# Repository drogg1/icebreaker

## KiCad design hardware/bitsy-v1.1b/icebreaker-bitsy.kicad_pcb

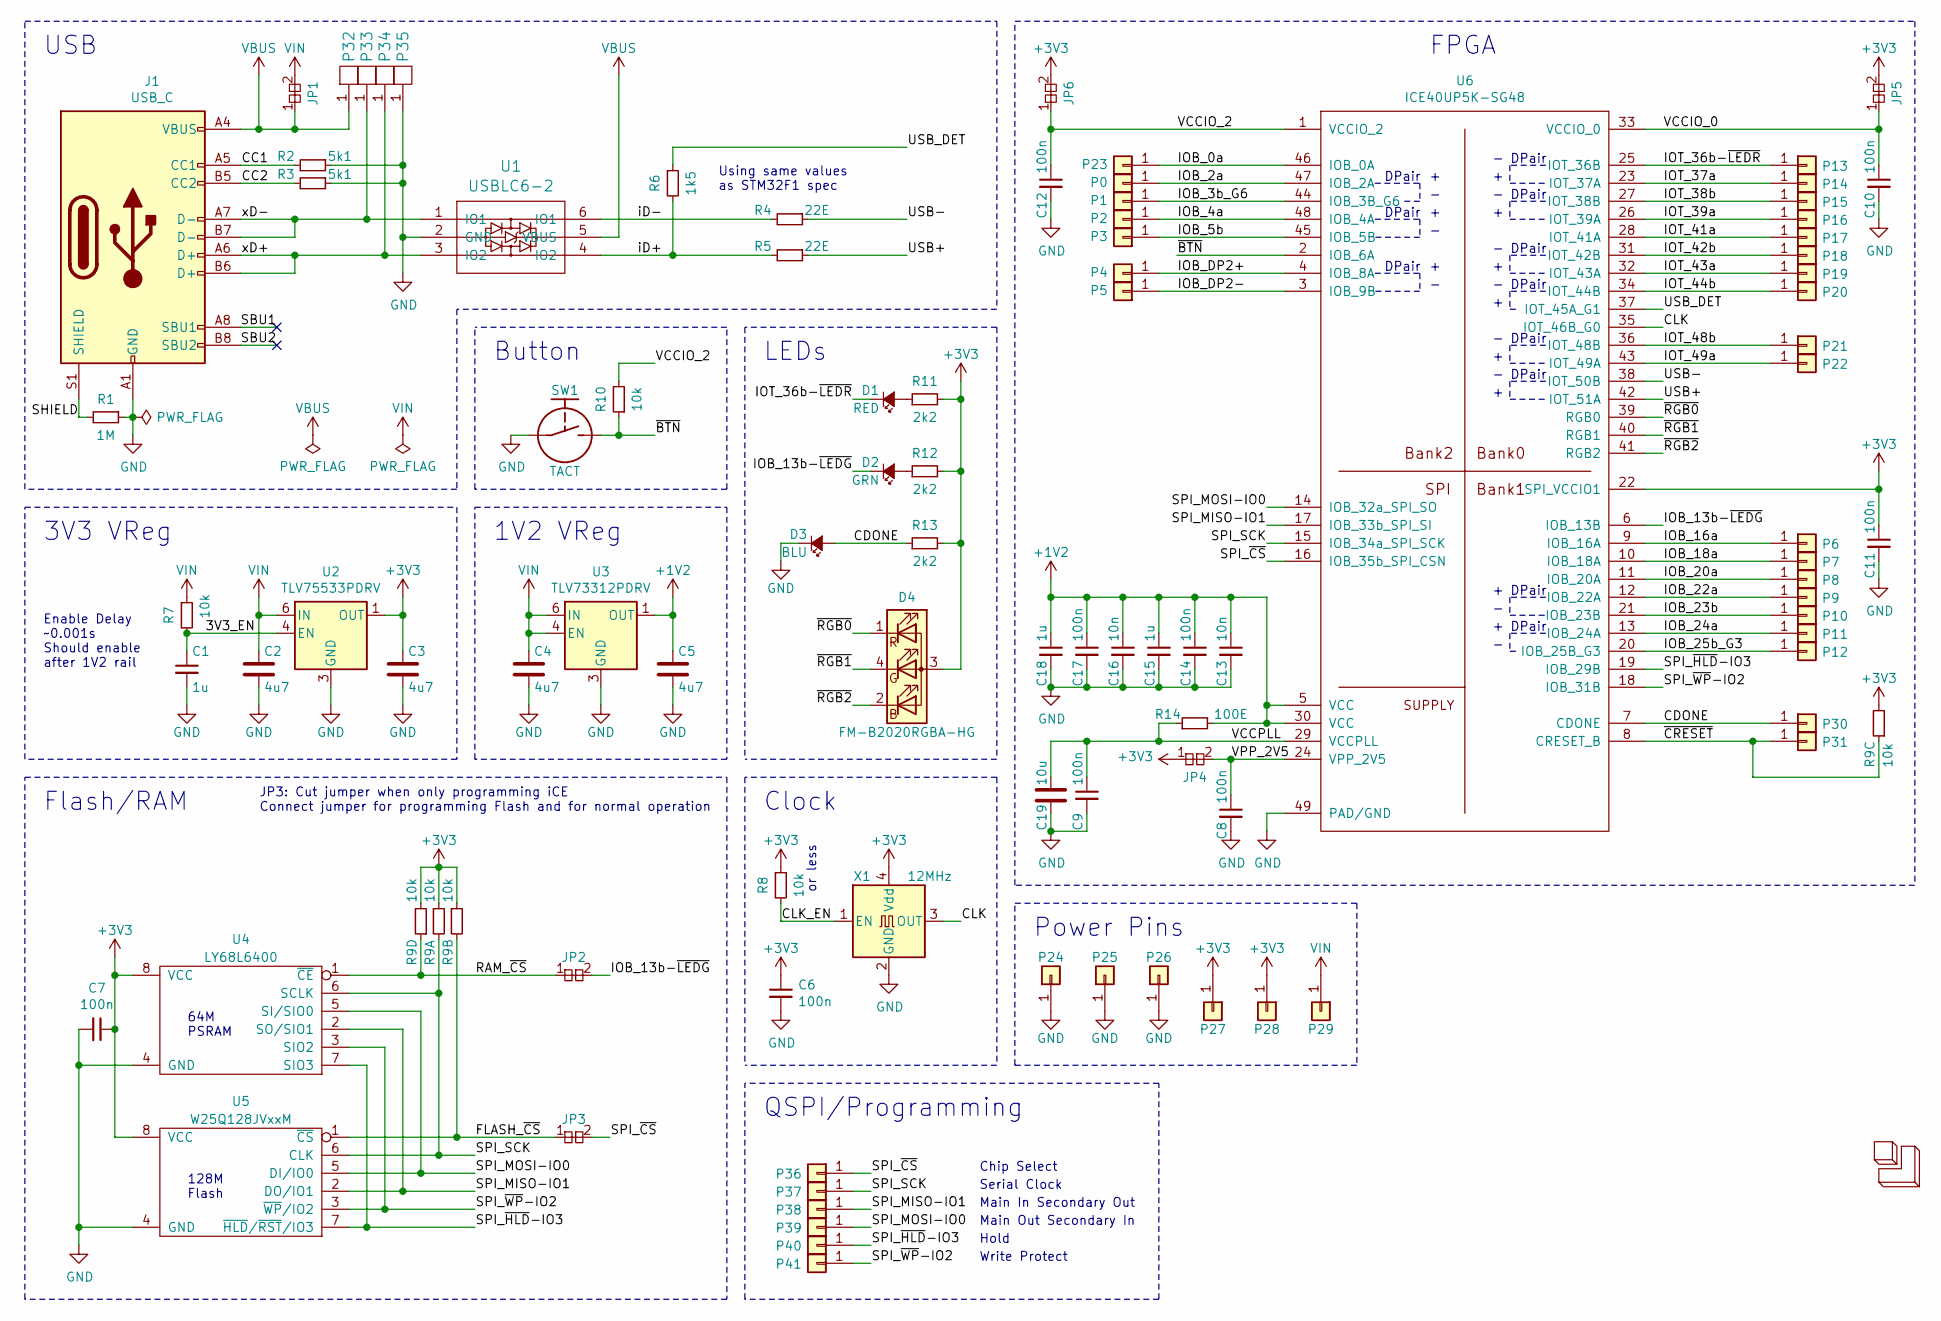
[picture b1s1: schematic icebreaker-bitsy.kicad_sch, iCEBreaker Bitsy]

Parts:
C1, C15, C18: 1u; C_0402
C2, C3, C4, C5: 4u7; C_0603
C6, C7, C8, C9, C10, C11, C12, C14, C17: 100n; C_0402
C13, C16: 10n; C_0402
C19: 10u; C_0603
D1: RED; D_0603
D2: GRN; D_0603
D3: BLU; D_0603
D4: FM-B2020RGBA-HG; LED_TRI_2020
J1: USB_C; USB_C_Receptacle_HRO_TYPE-C-31-M-12
JP1: Jumper; J_NC_0603_40
JP2, JP3: Jumper; J_NC_0402_15
JP4: Jumper; J_NC_0402_30
JP5, JP6: Jumper; J_NC_0603_30
LOGO1: 1BitSquared; 1b2_Logo_SilkS_6.5mm
P0: 0; Pin_Header_Straight_Round_1x01_Castellated
P1: 1; Pin_Header_Straight_Round_1x01_Castellated
P2: 2; Pin_Header_Straight_Round_1x01_Castellated
P3: 3; Pin_Header_Straight_Round_1x01_Castellated
P4: 4; Pin_Header_Straight_Round_1x01_Castellated
P5: 5; Pin_Header_Straight_Round_1x01_Castellated
P6: 6; Pin_Header_Straight_Round_1x01_Castellated
P7: 7; Pin_Header_Straight_Round_1x01_Castellated
P8: 8; Pin_Header_Straight_Round_1x01_Castellated
P9: 9; Pin_Header_Straight_Round_1x01_Castellated
P10: 10; Pin_Header_Straight_Round_1x01_Castellated
P11: 11; Pin_Header_Straight_Round_1x01_Castellated
P12: 12; Pin_Header_Straight_Round_1x01_Castellated
P13: 13; Pin_Header_Straight_Round_1x01_Castellated
P14: 14; Pin_Header_Straight_Round_1x01_Castellated
P15: 15; Pin_Header_Straight_Round_1x01_Castellated
P16: 16; Pin_Header_Straight_Round_1x01_Castellated
P17: 17; Pin_Header_Straight_Round_1x01_Castellated
P18: 18; Pin_Header_Straight_Round_1x01_Castellated
P19: 19; Pin_Header_Straight_Round_1x01_Castellated
P20: 20; Pin_Header_Straight_Round_1x01_Castellated
P21: 21; Pin_Header_Straight_Round_1x01_Castellated
P22: 22; Pin_Header_Straight_Round_1x01_Castellated
P23: 23; Pin_Header_Straight_Round_1x01_Castellated
P24, P25, P26: GND; Pin_Header_Straight_Round_1x01_Castellated
P27, P28: 3V3; Pin_Header_Straight_Round_1x01_Castellated
P29: VIN; Pin_Header_Straight_Round_1x01_Castellated
P30: CDONE; Pin_Header_Straight_Round_1x01_Castellated
P31: CRESET; Pin_Header_Straight_Round_1x01_Castellated
P32, P33, P34, P35: UP; PAD_SMD_1x2.65_ROUNDED
P36: CS; Pin_Header_Straight_Round_1x01
P37: SCK; Pin_Header_Straight_Round_1x01
P38: MISO; Pin_Header_Straight_Round_1x01
P39: MOSI; Pin_Header_Straight_Round_1x01
P40: IO3; PAD_SMD_R_1x1
P41: IO2; PAD_SMD_R_1x1
R1: 1M; R_0402
R2, R3: 5k1; R_0402
R4, R5: 22E; R_0402
R6: 1k5; R_0402
R7, R8, R10: 10k; R_0402
R9: 10k; R_Array_Convex_4x0402
R11, R12, R13: 2k2; R_0402
R14: 100E; R_0402
SW1: TACT; SW_SPST_3x4x2.5
U1: USBLC6-2; SOT-666
U2: TLV75533PDRV; WSON-6-1EP_2x2mm_P0.65mm_EP1x1.6mm
U3: TLV73312PDRV; WSON-6-1EP_2x2mm_P0.65mm_EP1x1.6mm
U4: LY68L6400; SOIC-8_3.9x4.9mm_P1.27mm
U5: W25Q128JVxxM; WSON-8-1EP_6x5mm_P1.27mm_EP3.4x4.3mm
U6: ICE40UP5K-SG48; QFN-48-1EP_7x7mm_Pitch0.5mm
X1: 12MHz; Oscillator_SMD_SCTF_S2DXX-4Pin_2.5x2.0mm

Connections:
+1V2: C5.1, C13.1, C14.1, C15.1, C16.1, C17.1, C18.1, R14.2, U3.1 (OUT), U6.5 (VCC), U6.30 (VCC)
+3V3: C3.1, C6.1, C7.1, C11.1, D4.3 (A), JP4.1, JP5.2, JP6.2, P27.1, P28.1, R8.1, R9.1, R9.3, R9.6, R9.8, R11.2, R12.2, R13.2, U2.1 (OUT), U4.8 (VCC), U5.8 (VCC), U6.22 (SPI_VCCIO1), X1.4 (Vdd)
/3V3_EN: C1.1, R7.2, U2.4 (EN)
/CC1: J1.A5 (CC1), R2.2
/CC2: J1.B5 (CC2), R3.2
/CDONE: D3.A, P30.1, R13.1, U6.7 (CDONE)
/CLK: U6.35 (IOT_46B_G0), X1.3 (OUT)
/CLK_EN: R8.2, X1.1 (EN)
/FLASH_~CS: JP3.1, R9.4, U5.1 (~CS)
/IOB_0a: P23.1, U6.46 (IOB_0A)
/IOB_2a: P0.1, U6.47 (IOB_2A)
/IOB_3b_G6: P1.1, U6.44 (IOB_3B_G6)
/IOB_4a: P2.1, U6.48 (IOB_4A)
/IOB_5b: P3.1, U6.45 (IOB_5B)
/IOB_13b-~LEDG: D2.C, JP2.2, U6.6 (IOB_13B)
/IOB_16a: P6.1, U6.9 (IOB_16A)
/IOB_18a: P7.1, U6.10 (IOB_18A)
/IOB_20a: P8.1, U6.11 (IOB_20A)
/IOB_22a: P9.1, U6.12 (IOB_22A)
/IOB_23b: P10.1, U6.21 (IOB_23B)
/IOB_24a: P11.1, U6.13 (IOB_24A)
/IOB_25b_G3: P12.1, U6.20 (IOB_25B_G3)
/IOB_DP2+: P4.1, U6.4 (IOB_8A)
/IOB_DP2-: P5.1, U6.3 (IOB_9B)
/IOT_36b-~LEDR: D1.C, P13.1, U6.25 (IOT_36B)
/IOT_37a: P14.1, U6.23 (IOT_37A)
/IOT_38b: P15.1, U6.27 (IOT_38B)
/IOT_39a: P16.1, U6.26 (IOT_39A)
/IOT_41a: P17.1, U6.28 (IOT_41A)
/IOT_42b: P18.1, U6.31 (IOT_42B)
/IOT_43a: P19.1, U6.32 (IOT_43A)
/IOT_44b: P20.1, U6.34 (IOT_44B)
/IOT_48b: P21.1, U6.36 (IOT_48B)
/IOT_49a: P22.1, U6.43 (IOT_49A)
/RAM_~CS: JP2.1, R9.7, U4.1 (~CE)
/SBU1: J1.A8 (SBU1)
/SBU2: J1.B8 (SBU2)
/SHIELD: J1.S1 (SHIELD), R1.2
/SPI_MISO-IO1: P38.1, U4.2 (SO/SIO1), U5.2 (DO/IO1), U6.17 (IOB_33b_SPI_SI)
/SPI_MOSI-IO0: P39.1, U4.5 (SI/SIO0), U5.5 (DI/IO0), U6.14 (IOB_32a_SPI_SO)
/SPI_SCK: P37.1, R9.2, U4.6 (SCLK), U5.6 (CLK), U6.15 (IOB_34a_SPI_SCK)
/SPI_~CS: JP3.2, P36.1, U6.16 (IOB_35b_SPI_CSN)
/SPI_~HLD~-IO3: P40.1, U4.7 (SIO3), U5.7 (~HLD~/~RST~/IO3), U6.19 (IOB_29B)
/SPI_~WP~-IO2: P41.1, U4.3 (SIO2), U5.3 (~WP~/IO2), U6.18 (IOB_31B)
/USB+: R5.1, U6.42 (IOT_51A)
/USB-: R4.1, U6.38 (IOT_50B)
/USB_DET: R6.1, U6.37 (IOT_45A_G1)
/VCCIO_0: C10.1, JP5.1, U6.33 (VCCIO_0)
/VCCIO_2: C12.1, JP6.1, R10.2, U6.1 (VCCIO_2)
/VCCPLL: C9.1, C19.1, R14.1, U6.29 (VCCPLL)
/VPP_2V5: C8.1, JP4.2, U6.24 (VPP_2V5)
/iD+: R5.2, R6.2, U1.4 (IO2)
/iD-: R4.2, U1.6 (IO1)
/xD+: J1.A6 (D+), J1.B6 (D+), P34.1 (PAD), U1.3 (IO2)
/xD-: J1.A7 (D-), J1.B7 (D-), P33.1 (PAD), U1.1 (IO1)
/~BTN: R10.1, SW1.2, U6.2 (IOB_6A)
/~CRESET: P31.1, R9.5, U6.8 (CRESET_B)
/~RGB0: D4.1 (RK), U6.39 (RGB0)
/~RGB1: D4.4 (GK), U6.40 (RGB1)
/~RGB2: D4.2 (BK), U6.41 (RGB2)
GND: C1.2, C2.2, C3.2, C4.2, C5.2, C6.2, C7.2, C8.2, C9.2, C10.2, C11.2, C12.2, C13.2, C14.2, C15.2, C16.2, C17.2, C18.2, C19.2, D3.C, J1.A1 (GND), J1.A12 (GND), J1.B1 (GND), J1.B12 (GND), P24.1, P25.1, P26.1, P35.1 (PAD), R1.1, R2.1, R3.1, SW1.1, U1.2 (GND), U2.3 (GND), U2.7 (GND), U3.3 (GND), U3.7 (GND), U4.4 (GND), U5.4 (GND), U6.49 (PAD/GND), X1.2 (GND)
unnamed: D1.A, R11.1
unnamed: D2.A, R12.1
VBUS: J1.A4 (VBUS), J1.A9 (VBUS), J1.B4 (VBUS), J1.B9 (VBUS), JP1.1, P32.1 (PAD), U1.5 (VBUS)
VIN: C2.1, C4.1, JP1.2, P29.1, R7.1, U2.6 (IN), U3.4 (EN), U3.6 (IN)

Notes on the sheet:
USB
3V3 VReg
Enable Delay ~~0.001s Should enable after 1V2 rail
Flash/RAM
64M PSRAM
128M Flash
JP3: Cut jumper when only programming iCE Connect jumper for programming Flash and for normal operation
Button
1V2 VReg
Using same values as STM32F1 spec
LEDs
Clock
QSPI/Programming
or less
Chip Select
Serial Clock
Main In Secondary Out
Main Out Secondary In
Hold
Write Protect
Power Pins
DPair
FPGA

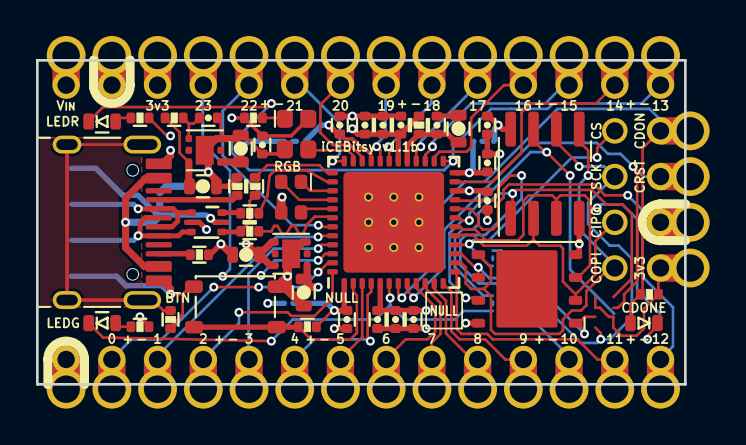
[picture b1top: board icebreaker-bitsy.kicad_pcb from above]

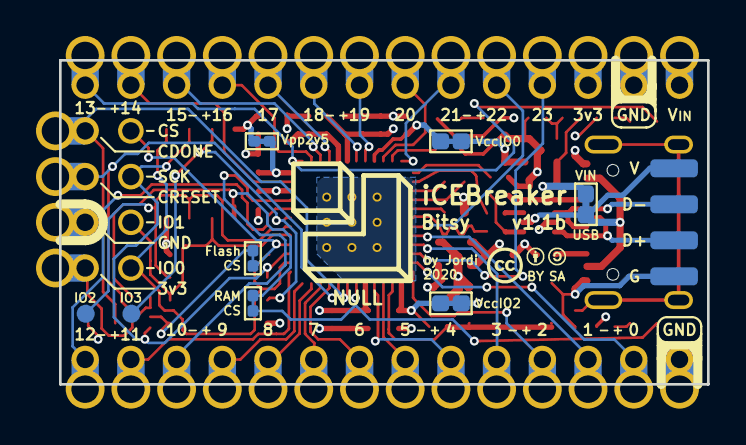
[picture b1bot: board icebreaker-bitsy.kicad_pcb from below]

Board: 4 copper layers, 36.0 x 18.0 mm, 94 parts (13 on the bottom side), 63 nets.

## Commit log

2021-01-15 Rerouted USB Diff Pair and added BCop GND Pour
2021-01-15 Exploring DiffPair Routing

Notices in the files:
hardware/bitsy-v1.1b/icebreaker-bitsy.kicad_pcb:
© 2018-2020 1BitSquared
© 2018-2020 Piotr Esden-Tempski
© 2020 Jordi Pakey-Rodriguez
License: CC BY-SA 4.0
